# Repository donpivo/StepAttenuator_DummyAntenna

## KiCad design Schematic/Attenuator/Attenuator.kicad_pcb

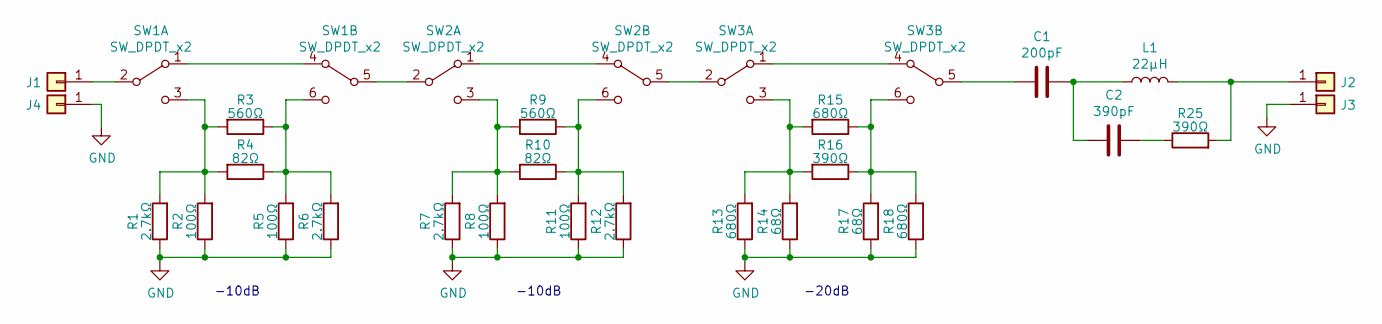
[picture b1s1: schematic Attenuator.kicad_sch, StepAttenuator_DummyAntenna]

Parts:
C1: 200pF; C_0603_1608Metric_Pad1.08x0.95mm_HandSolder
C2: 390pF; C_0603_1608Metric_Pad1.08x0.95mm_HandSolder
J1, J2, J3, J4: Conn_01x01; SolderWirePad_1.3
L1: 22µH; L_0603_1608Metric_Pad1.05x0.95mm_HandSolder
R1, R6, R7, R12: 2.7kΩ; R_0603_1608Metric_Pad1.05x0.95mm_HandSolder
R2, R5, R8, R11: 100Ω; R_0603_1608Metric_Pad1.05x0.95mm_HandSolder
R3, R9: 560Ω; R_0603_1608Metric_Pad1.05x0.95mm_HandSolder
R4, R10: 82Ω; R_0603_1608Metric_Pad1.05x0.95mm_HandSolder
R13, R15, R18: 680Ω; R_0603_1608Metric_Pad1.05x0.95mm_HandSolder
R14, R17: 68Ω; R_0603_1608Metric_Pad1.05x0.95mm_HandSolder
R16, R25: 390Ω; R_0603_1608Metric_Pad1.05x0.95mm_HandSolder
SW1, SW2, SW3: SW_DPDT_x2; SW_Toggle_DPDT_2MD1T1B1M2QES-5

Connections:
GND: J3.1, J4.1, R1.1, R2.1, R5.1, R6.1, R7.1, R8.1, R11.1, R12.1, R13.1, R14.1, R17.1, R18.1
unnamed: C1.1, C2.2, L1.1
unnamed: C2.1, R25.1
unnamed: J1.1, SW1.2 (B)
unnamed: J2.1, L1.2, R25.2
unnamed: SW1.1 (A), SW1.4 (A)
unnamed: R1.2, R2.2, R3.2, R4.2, SW1.3 (C)
unnamed: SW1.5 (B), SW2.2 (B)
unnamed: R3.1, R4.1, R5.2, R6.2, SW1.6 (C)
unnamed: SW2.1 (A), SW2.4 (A)
unnamed: R7.2, R8.2, R9.2, R10.2, SW2.3 (C)
unnamed: SW2.5 (B), SW3.2 (B)
unnamed: R9.1, R10.1, R11.2, R12.2, SW2.6 (C)
unnamed: SW3.1 (A), SW3.4 (A)
unnamed: R13.2, R14.2, R15.2, R16.2, SW3.3 (C)
unnamed: C1.2, SW3.5 (B)
unnamed: R15.1, R16.1, R17.2, R18.2, SW3.6 (C)

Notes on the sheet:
-10dB
-20dB

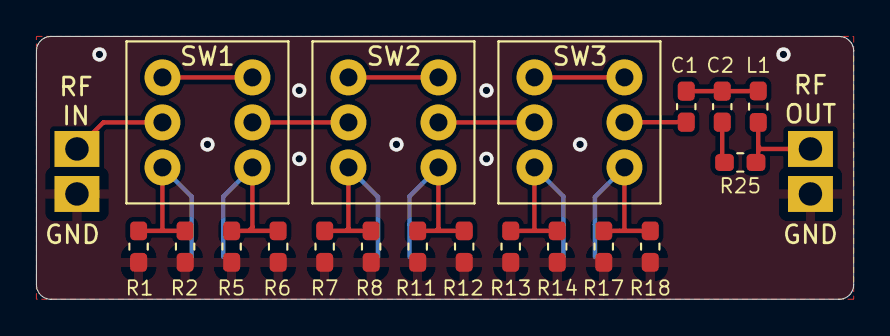
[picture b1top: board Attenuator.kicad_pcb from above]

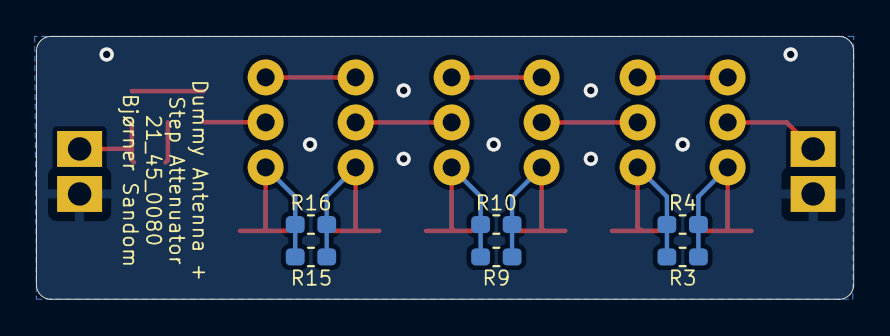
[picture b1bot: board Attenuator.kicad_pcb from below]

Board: 2 copper layers, 45.4 x 14.6 mm, 29 parts (6 on the bottom side), 17 nets.

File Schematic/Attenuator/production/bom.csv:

Designator,Footprint,Quantity,Value,LCSC Part #
C1,0603,1,200pF,
C2,0603,1,390pF,
"J1, J2, J3, J4",SolderWirePad_1.3,4,Conn_01x01,
L1,0603,1,22µH,
"R1, R12, R6, R7",0603,4,2.7kΩ,
"R10, R4",0603,2,82Ω,
"R11, R2, R5, R8",0603,4,100Ω,
"R13, R15, R18",0603,3,680Ω,
"R14, R17",0603,2,68Ω,
"R16, R25",0603,2,390Ω,
"R3, R9",0603,2,560Ω,
"SW1, SW2, SW3",SW_Toggle_DPDT_2MD1T1B1M2QES-5,3,SW_DPDT_x2,

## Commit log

2023-09-13 Updated production files
